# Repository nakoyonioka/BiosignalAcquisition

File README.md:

# Multi-Channel Biosignal Acquisition System with DRL

This project provides a hardware platform for capturing physiological signals such as EEG or ECG. It features multiple input channels with dedicated analog signal conditioning stages (amplification, filtering) to prepare the signals for digitization. A key aspect is the inclusion of a Driven Right Leg (DRL) circuit on Channel 1, a common technique in biopotential measurements to improve signal quality by reducing common-mode interference. The system also incorporates robust power management, supporting battery operation and providing necessary regulated voltage rails, before signals are passed to an Analog-to-Digital Converter (ADC) for digital processing via either isolated or non-isolated SPI.

## Features

- **Multi-Channel Input:** Supports acquisition from 4 independent biosignal channels.
- **Analog Front-End:** Each channel includes amplification and filtering stages (high-pass and low-pass filters).
- **Driven Right Leg (DRL):** Channel 1 features a DRL circuit for enhanced common-mode noise rejection.
- **Signal Conditioning:** Band-pass filtering.
- **Analog-to-Digital Conversion:** Utilizes an onboard ADC (**AD7682BCP**) to convert analog signals to digital data.
- **Digital Interface:** Provides SPI communication interface for connecting to a microcontroller or processor. Includes options for isolated or non-isolated SPI.
- **Power Management:**
  - Battery input and switching.
  - Battery protection IC (BQ29723).
  - Boost converter (TPS61232) for generating +5V from a lower battery voltage.
  - RED3025 and LM2776 IC for generating reference voltagse for ADC and opamps
  - Virtual ground generation for the analog circuitry.

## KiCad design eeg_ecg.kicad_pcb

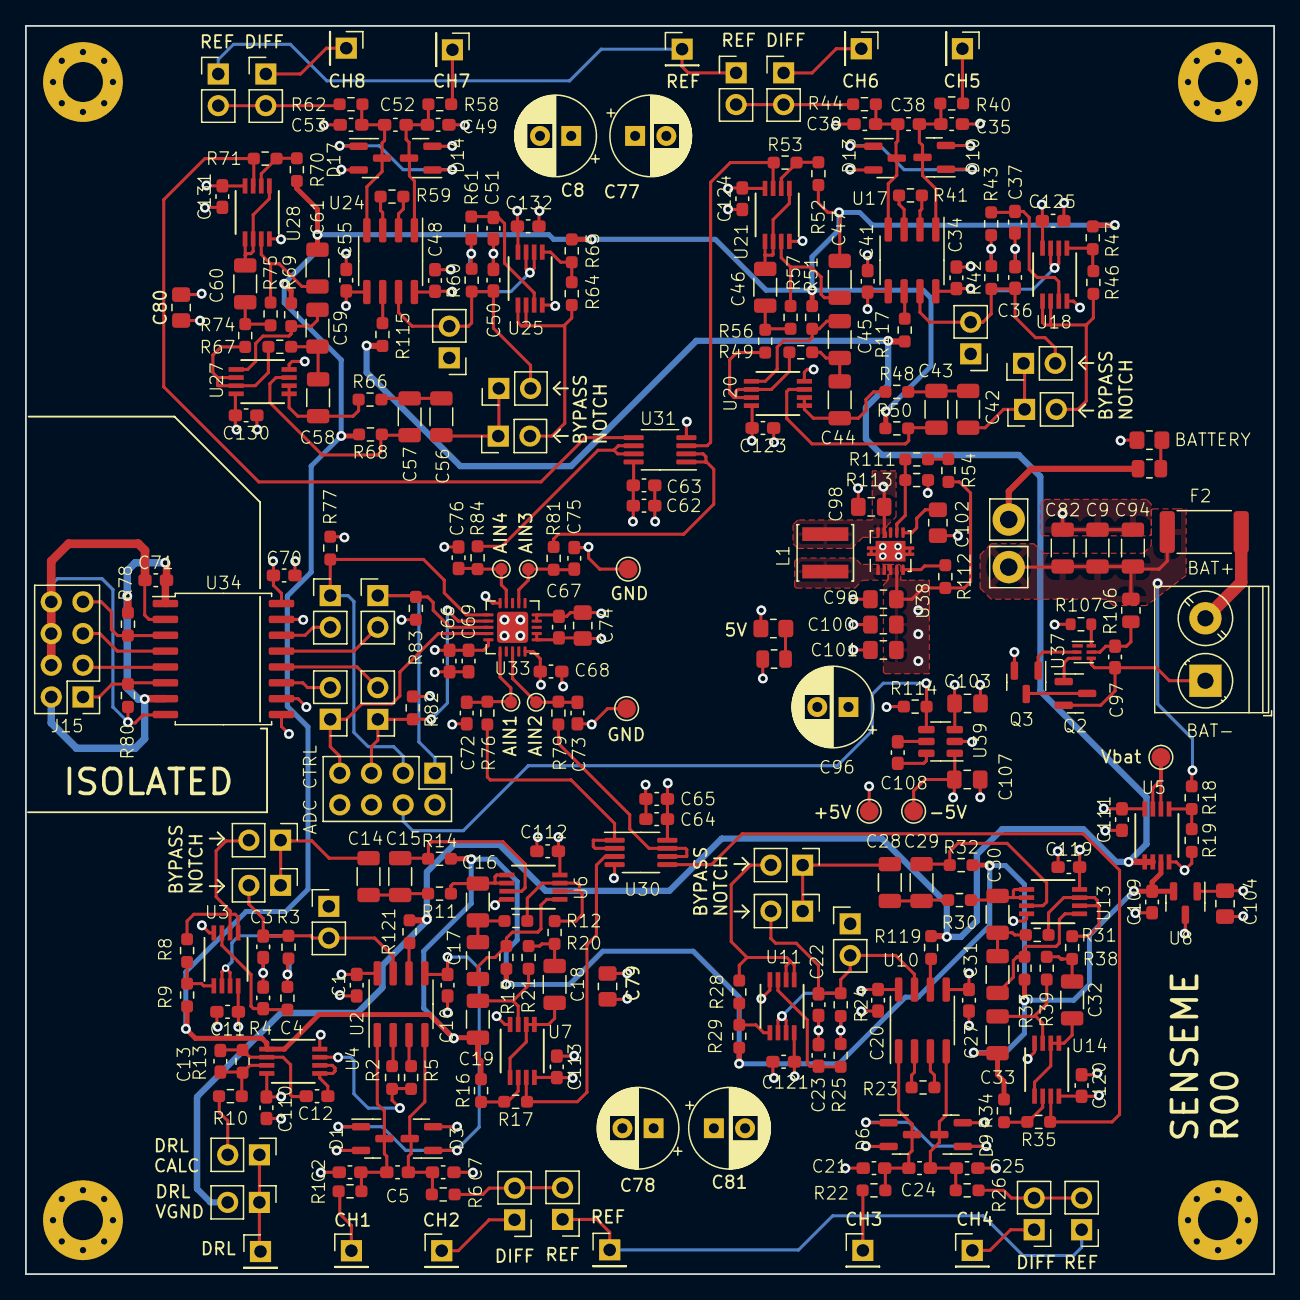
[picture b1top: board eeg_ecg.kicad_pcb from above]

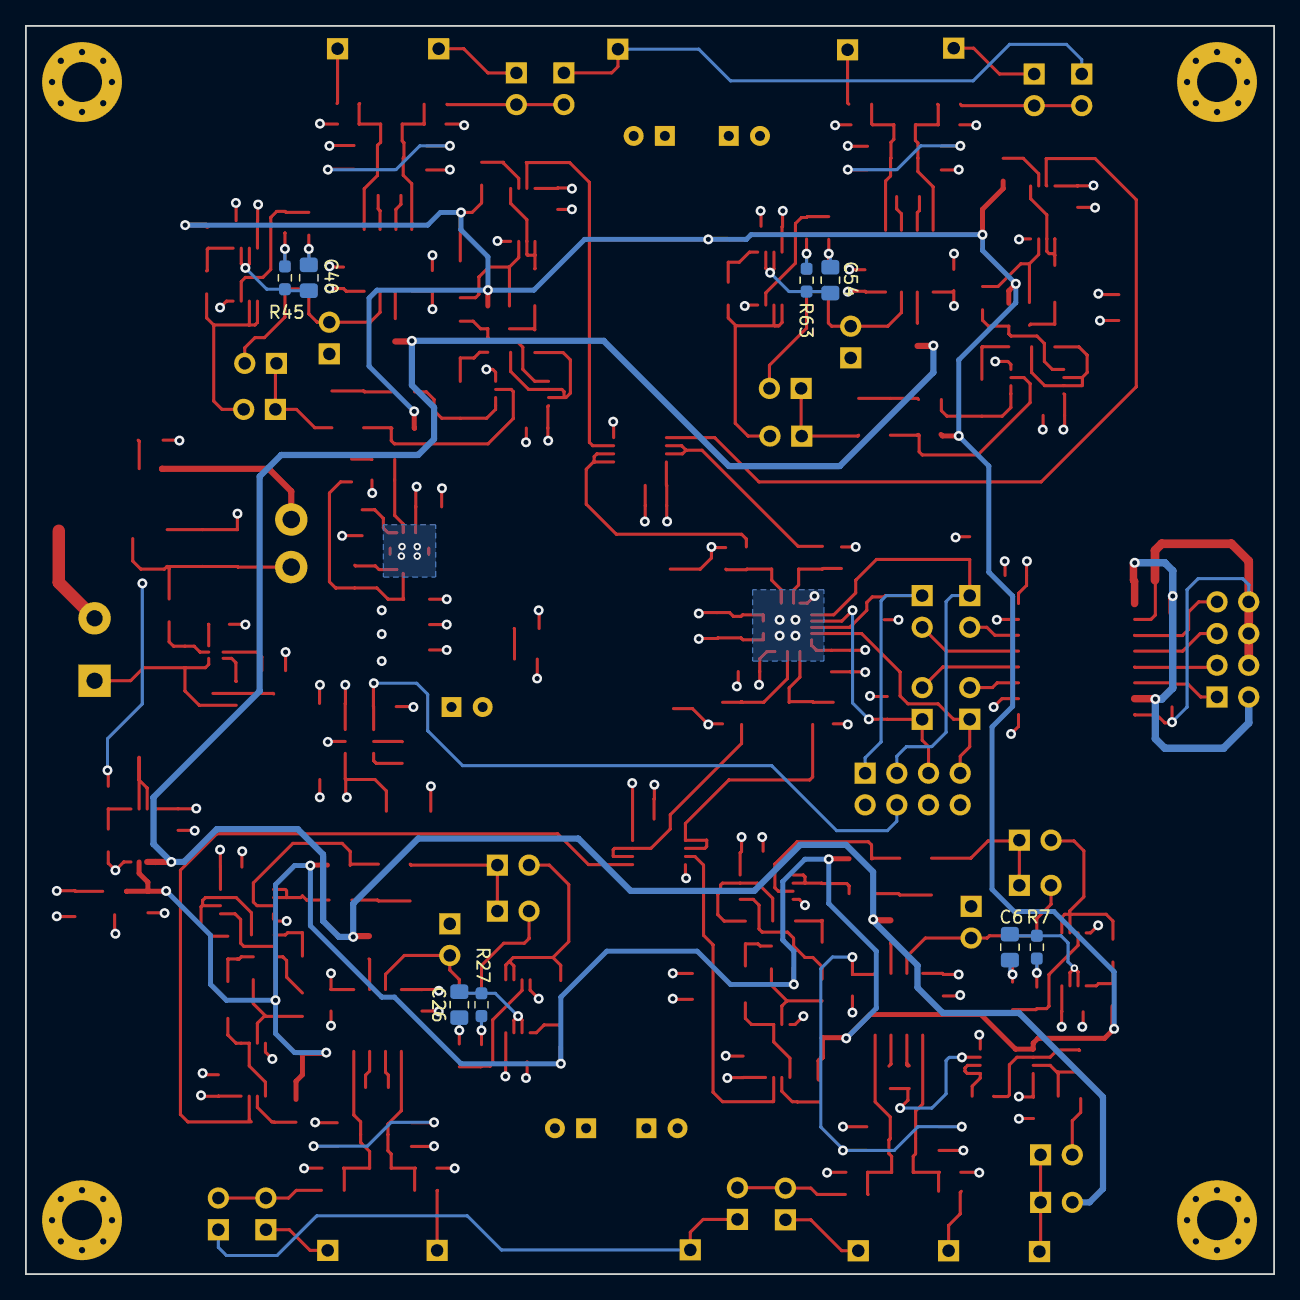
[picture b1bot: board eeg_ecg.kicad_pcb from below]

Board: 4 copper layers, 100.0 x 100.0 mm, 294 parts (8 on the bottom side), 163 nets.

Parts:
C1, C10, C11, C20, C27, C34, C41, C48, C55, C62, C64, C67, C68, C69, C70, C71, C97, C109, C110, C111, C112, C113, C119, C120, C121, C123, C124, C125, C130, C131, C132: 100nF; C_0603_1608Metric_Pad1.08x0.95mm_HandSolder
C2, C7, C21, C25, C35, C39, C49, C53: 100pF; C_0603_1608Metric_Pad1.08x0.95mm_HandSolder
C3, C4, C5, C22, C23, C24, C36, C37, C38, C50, C51, C52: 1nF; C_0603_1608Metric_Pad1.08x0.95mm_HandSolder
C6, C26, C40, C54: 22nF; C_0805_2012Metric_Pad1.18x1.45mm_HandSolder
C8, C77, C78, C81, C96: 100uF; CP_Radial_D6.3mm_P2.50mm
C9, C82, C94: 22uF; C_1206_3216Metric
C12, C108: 1uF; C_0603_1608Metric_Pad1.08x0.95mm_HandSolder
C13: 220nF; C_0603_1608Metric_Pad1.08x0.95mm_HandSolder
C14, C15, C16, C17, C19, C28, C29, C30, C31, C33, C42, C43, C44, C45, C47, C56, C57, C58, C59, C61: 100nF; C_1206_3216Metric
C18, C32, C46, C60: 220nF; C_1206_3216Metric
C63, C65, C66: 10uF; C_0603_1608Metric_Pad1.08x0.95mm_HandSolder
C72, C73, C75, C76: 10nF; C_0603_1608Metric_Pad1.08x0.95mm_HandSolder
C74: 10uF; C_0805_2012Metric_Pad1.18x1.45mm_HandSolder
C79, C80, C98, C99, C100, C101, C103, C104, C107: 22uF; C_0805_2012Metric_Pad1.18x1.45mm_HandSolder
C102: 10nF; C_0805_2012Metric_Pad1.18x1.45mm_HandSolder
D1, D3, D6, D9, D10, D13, D14, D17: BAV199; SOT-23
D2, D4: GREEN; R_0805_2012Metric_Pad1.20x1.40mm_HandSolder
F2: 5A; R_2512_6332Metric
H1, H2, H3, H4: MountingHole_Pad; MountingHole_3.2mm_M3_Pad_Via
J1, J2, J3, J4, J5, J6, J7, J8, J9, J10, J12: Conn_01x01; PinHeader_1x01_P2.54mm_Vertical
J11, J15: Conn_02x04_Odd_Even; PinHeader_2x04_P2.54mm_Vertical
J29, J30: Conn_01x01_Pin; Pin_D1.4mm_L8.5mm_W2.8mm_FlatFork
J33: Screw_Terminal_01x02; TerminalBlock_Phoenix_PT-1,5-2-5.0-H_1x02_P5.00mm_Horizontal
JP1, JP2, JP3, JP4, JP5, JP6, JP7, JP8, JP9, JP10, JP11, JP12, JP13, JP14, JP15, JP16, JP17, JP18, JP19, JP20, JP21, JP22, JP31, JP32, JP33, JP34: Jumper_2_Open; PinHeader_1x02_P2.54mm_Vertical
L1: SWPA4030S1R0NT/1uH; L_Sunlord_SWPA4030S
Q2, Q3: AO3400A; SOT-23
R1, R6, R18, R19, R22, R26, R40, R44, R58, R62, R77, R78, R80, R82, R83, R114: 10k; R_0603_1608Metric_Pad0.98x0.95mm_HandSolder
R2, R5: 220; R_0603_1608Metric_Pad0.98x0.95mm_HandSolder
R3, R4, R24, R25, R42, R43, R60, R61, R111: 330k; R_0603_1608Metric_Pad0.98x0.95mm_HandSolder
R7, R27, R45, R63: 150k; R_0603_1608Metric_Pad0.98x0.95mm_HandSolder
R8, R28, R46, R64: 20k; R_0603_1608Metric_Pad0.98x0.95mm_HandSolder
R9, R15, R29, R33, R47, R51, R65, R69: 82k; R_0603_1608Metric_Pad0.98x0.95mm_HandSolder
R10, R17, R35, R53, R71, R113: 100k; R_0603_1608Metric_Pad0.98x0.95mm_HandSolder
R11, R30, R48, R66: 30k; R_0603_1608Metric_Pad0.98x0.95mm_HandSolder
R12, R31, R49, R67: 12k; R_0603_1608Metric_Pad0.98x0.95mm_HandSolder
R13, R112: 1Meg; R_0603_1608Metric_Pad0.98x0.95mm_HandSolder
R14, R32, R50, R68: 33k; R_0603_1608Metric_Pad0.98x0.95mm_HandSolder
R16, R34, R52, R70: 1k; R_0603_1608Metric_Pad0.98x0.95mm_HandSolder
R20, R21, R38, R39, R56, R57, R74, R75: 15k; R_0603_1608Metric_Pad0.98x0.95mm_HandSolder
R23, R41, R59: 510; R_0603_1608Metric_Pad0.98x0.95mm_HandSolder
R36, R37, R106: 330R; R_0805_2012Metric
R54: 75k; R_0603_1608Metric_Pad0.98x0.95mm_HandSolder
R76, R79, R81, R84: 100; R_0603_1608Metric_Pad0.98x0.95mm_HandSolder
R107: 2k7; R_0603_1608Metric
R115, R117, R119, R121: 0R; R_0603_1608Metric_Pad0.98x0.95mm_HandSolder
TP1, TP2, TP3, TP4, TP5: TestPoint; TestPoint_Pad_D1.5mm
TP6, TP7, TP8, TP9: TestPoint; TestPoint_Pad_D1.0mm
U2, U10, U17, U24: AD8421ARZ; SOIC-8_3.9x4.9mm_P1.27mm
U3, U4, U5, U6, U7, U11, U13, U14, U18, U20, U21, U25, U27, U28: AD8606ARMZ-R7; AD8606ARMZ
U8: REF3025; SOT-23
U30, U31: ADA4807-2ARM; MSOP-8_3x3mm_P0.65mm
U33: AD7682BCP; LFCSP-20-1EP_4x4mm_P0.5mm_EP2.5x2.5mm
U34: ISO7341C; SOIC-16W_7.5x10.3mm_P1.27mm
U37: BQ29723; WSON-6_1.5x1.5mm_P0.5mm
U38: TPS61230DRC; Texas_S-PVSON-N10_ThermalVias
U39: LM2776; SOT-23-6

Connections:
+5V: C1.2, C8.1, C11.2, C20.2, C34.2, C48.2, C62.2, C63.2, C64.2, C65.2, C66.2, C67.2, C68.2, C69.2, C70.2, C74.2, C77.1, C78.1, C81.1, C96.1, C99.2, C100.2, C101.2, C103.2, C104.2, C110.2, C111.2, C112.2, C113.2, C119.2, C120.2, C121.2, C123.2, C124.2, C125.2, C130.2, C131.2, C132.2, D1.2 (K), D3.2 (K), D6.2 (K), D9.2 (K), D10.2 (K), D13.2 (K), D14.2 (K), D17.2 (K), J11.2, R36.1, R54.1, R77.1, R112.2, R114.1, TP2.1, U2.8 (Vs+), U3.8 (V+), U4.8 (V+), U5.8 (V+), U6.8 (V+), U7.8 (V+), U8.1 (IN), U10.8 (Vs+), U11.8 (V+), U13.8 (V+), U14.8 (V+), U17.8 (Vs+), U18.8 (V+), U20.8 (V+), U21.8 (V+), U24.8 (Vs+), U25.8 (V+), U27.8 (V+), U28.8 (V+), U30.8 (V+), U31.8 (V+), U33.1 (VDD), U33.2 (REF), U33.15 (VIO), U33.20 (VDD), U34.10 (EN2), U34.16 (VCC2), U38.3 (VOUT), U38.4 (VOUT), U39.3 (VIN)
+5VP: C71.2, J15.2, R78.1, U34.1 (VCC1), U34.7 (EN1)
+BATT: C9.1, C82.1, C94.1, F2.2, J29.1, R18.1, R106.2
-5V: C10.2, C27.2, C41.2, C55.2, C79.2, C80.2, C107.2, D1.1 (A), D3.1 (A), D6.1 (A), D9.1 (A), D10.1 (A), D13.1 (A), D14.1 (A), D17.1 (A), TP3.1, U2.5 (Vs-), U10.5 (Vs-), U17.5 (Vs-), U24.5 (Vs-), U39.1 (VOUT)
/ADC and control/ADCCLK: J11.1, JP20.1 (A), R83.1, U33.13 (SCK)
/ADC and control/ADCCSn: J11.3, JP19.1 (A), R77.2, U33.11 (CNV)
/ADC and control/ADCDIN: J11.5, JP21.1 (A), R82.1, U33.12 (DIN)
/ADC and control/ADCDO: J11.7, JP22.1 (A), U33.14 (SDO)
/ADC and control/AIN1: C72.2, R76.1, TP6.1, U33.16 (IN0)
/ADC and control/AIN2: C73.2, R79.1, TP7.1, U33.18 (IN1)
/ADC and control/AIN3: C75.2, R81.1, TP8.1, U33.7 (IN2)
/ADC and control/AIN4: C76.2, R84.1, TP9.1, U33.9 (IN3)
/ADC and control/CH1: R17.1, U7.7, U30.3 (+)
/ADC and control/CH2: R35.1, U14.7, U30.5 (+)
/ADC and control/CH3: R53.1, U21.7, U31.3 (+)
/ADC and control/CH4: R71.1, U28.7, U31.5 (+)
/ADC and control/ISO_CLK: J15.5, U34.4 (INB)
/ADC and control/ISO_CSn: J15.7, R78.2, U34.3 (INA)
/ADC and control/ISO_MISO: J15.1, R80.1, U34.6 (OUTD)
/ADC and control/ISO_MOSI: J15.3, U34.5 (INC)
/Battery input/BATn: C97.2, J33.1, Q2.2 (S), U37.4 (VSS)
/Battery input/BATp: F2.1, J33.2
/Battery input/Vbat: TP1.1, U5.6 (-), U5.7
/Channel 1 with DRL option/DRL: J6.1, JP5.1 (A), JP6.1 (A)
/Channel 1 with DRL option/HPF1: R12.1, R20.2, U6.6 (-), U6.7
/Channel 1 with DRL option/INPUT1: J1.1, R1.1
/Channel 1 with DRL option/INPUT2: J2.1, JP2.1 (A)
/Channel 1 with DRL option/NOTCH1: JP3.2 (B), R8.1, U3.1, U3.2 (-)
/Channel 2/HPF2: R31.1, R38.2, U13.6 (-), U13.7
/Channel 2/INPUT3: J4.1, R22.1
/Channel 2/INPUT4: J5.1, JP8.1 (A)
/Channel 2/NOTCH2: JP11.2 (B), R28.1, U11.1, U11.2 (-)
/Channel 3/HPF3: R49.1, R56.2, U20.6 (-), U20.7
/Channel 3/INPUT5: J7.1, R40.1
/Channel 3/INPUT6: J8.1, JP12.1 (A)
/Channel 3/NOTCH3: JP17.2 (B), R46.1, U18.1, U18.2 (-)
/Channel 4/HPF4: R67.1, R74.2, U27.6 (-), U27.7
/Channel 4/INPUT7: J9.1, R58.1
/Channel 4/INPUT8: J10.1, JP16.1 (A)
/Channel 4/NOTCH4: JP33.2 (B), R64.1, U25.1, U25.2 (-)
/Power supply/EN5V: J11.4, R114.2, U39.4 (EN)
GND: C1.1, C2.1, C7.2, C8.2, C9.2, C10.1, C11.1, C20.1, C21.1, C25.2, C27.1, C34.1, C35.1, C39.2, C41.1, C48.1, C49.1, C53.2, C55.1, C62.1, C63.1, C64.1, C65.1, C66.1, C67.1, C68.1, C69.1, C70.1, C72.1, C73.1, C74.1, C75.1, C76.1, C77.2, C78.2, C79.1, C80.1, C81.2, C82.2, C94.2, C96.2, C98.1, C99.1, C100.1, C101.1, C102.1, C103.1, C104.1, C107.1, C109.1, C110.1, C111.1, C112.1, C113.1, C119.1, C120.1, C121.1, C123.1, C124.1, C125.1, C130.1, C131.1, C132.1, D2.1 (K), D4.1 (K), H1.1, H2.1, H3.1, H4.1, J11.6, J11.8, JP1.1 (A), JP9.1 (A), JP15.1 (A), JP32.1 (A), Q3.2 (S), R19.2, R82.2, R83.2, R107.1, R113.2, TP4.1, TP5.1, U3.4 (V-), U4.4 (V-), U5.4 (V-), U6.4 (V-), U7.4 (V-), U8.3 (GND), U11.4 (V-), U13.4 (V-), U14.4 (V-), U18.4 (V-), U20.4 (V-), U21.4 (V-), U25.4 (V-), U27.4 (V-), U28.4 (V-), U30.4 (V-), U31.4 (V-), U33.4 (GND), U33.5 (GND), U33.10 (COM), U33.21 (EPAD), U34.9 (GND2), U34.15 (GND2), U38.11 (GND), U39.2 (GND)
GNDPWR: C71.1, J15.4, J15.6, J15.8, R80.2, U34.2 (GND1), U34.8 (GND1)
unnamed: C3.2, C4.1, R7.1
unnamed: C6.2, R3.1, R4.2
unnamed: C13.2, R10.2, R13.1, U4.7
unnamed: C14.1, C15.2, R11.2
unnamed: C16.1, C17.2, R12.2
unnamed: C18.1, R20.1, R21.2
unnamed: C22.2, C23.1, R27.1
unnamed: C26.2, R24.1, R25.2
unnamed: C28.1, C29.2, R30.2
unnamed: C30.1, C31.2, R31.2
unnamed: C32.1, R38.1, R39.2
unnamed: C36.2, C37.1, R45.1
unnamed: C40.2, R42.1, R43.2
unnamed: C42.1, C43.2, R48.2
unnamed: C44.1, C45.2, R49.2
unnamed: C46.1, R56.1, R57.2
unnamed: C50.2, C51.1, R63.1
unnamed: C54.2, R60.1, R61.2
unnamed: C56.1, C57.2, R66.2
unnamed: C58.1, C59.2, R67.2
unnamed: C60.1, R74.1, R75.2
unnamed: C2.2, C5.1, D1.3 (common), R1.2, U2.1 (-)
unnamed: D2.2 (A), R36.2
unnamed: C5.2, C7.1, D3.3 (common), R6.2, U2.4 (+)
unnamed: D4.2 (A), R37.2
unnamed: C21.2, C24.1, D6.3 (common), R22.2, U10.1 (-)
unnamed: C24.2, C25.1, D9.3 (common), R26.2, U10.4 (+)
unnamed: C35.2, C38.1, D10.3 (common), R40.2, U17.1 (-)
unnamed: C38.2, C39.1, D13.3 (common), R44.2, U17.4 (+)
unnamed: C49.2, C52.1, D14.3 (common), R58.2, U24.1 (-)
unnamed: C52.2, C53.1, D17.3 (common), R62.2, U24.4 (+)
unnamed: C3.1, JP1.2 (B), JP7.2 (B), R3.2, U2.7
unnamed: JP2.2 (B), JP4.2 (B), R6.1
unnamed: C14.2, JP3.1 (A), JP7.1 (A)
unnamed: JP5.2 (B), R10.1
unnamed: JP8.2 (B), JP10.2 (B), R26.1
unnamed: C28.2, JP11.1 (A), JP13.1 (A)
unnamed: JP12.2 (B), JP14.2 (B), R44.1
unnamed: C22.1, JP9.2 (B), JP13.2 (B), R24.2, U10.7
unnamed: C36.1, JP15.2 (B), JP31.2 (B), R42.2, U17.7
unnamed: JP16.2 (B), JP18.2 (B), R62.1
unnamed: C42.2, JP17.1 (A), JP31.1 (A)
unnamed: JP19.2 (B), U34.14 (OUTA)
unnamed: JP20.2 (B), U34.13 (OUTB)
unnamed: JP21.2 (B), U34.12 (OUTC)
unnamed: JP22.2 (B), U34.11 (IND)
unnamed: C50.1, JP32.2 (B), JP34.2 (B), R60.2, U24.7
unnamed: C56.2, JP33.1 (A), JP34.1 (A)
unnamed: L1.2, U38.1 (SW), U38.2 (SW)
unnamed: Q2.3 (D), Q3.3 (D)
unnamed: Q2.1 (G), U37.3 (Dout)
unnamed: Q3.1 (G), U37.2 (Cout)
unnamed: R2.2, U2.2 (Rg)
unnamed: R5.2, U2.3 (Rg)
unnamed: R23.1, U10.3 (Rg)
unnamed: R23.2, U10.2 (Rg)
unnamed: R41.1, U17.3 (Rg)
unnamed: R41.2, U17.2 (Rg)
unnamed: R59.1, U24.3 (Rg)
unnamed: R59.2, U24.2 (Rg)
unnamed: R54.2, R111.1
unnamed: R121.2, U2.6 (Ref)
unnamed: C4.2, R4.1, U3.3 (+)
unnamed: R8.2, R9.1, U3.5 (+)
unnamed: C6.1, R7.2, U3.6 (-), U3.7
unnamed: R2.1, R5.1, U4.3 (+)
unnamed: C12.2, U4.1, U4.2 (-)
unnamed: C12.1, C13.1, R13.2, U4.6 (-)
unnamed: R18.2, R19.1, U5.5 (+)
unnamed: C15.1, R14.1, U6.3 (+)
unnamed: C16.2, R11.1, U6.1, U6.2 (-)
unnamed: C17.1, R15.1, U6.5 (+)
unnamed: C19.2, R21.1, U7.3 (+)
unnamed: C18.2, U7.1, U7.2 (-), U7.5 (+)
unnamed: R16.1, R17.2, U7.6 (-)
unnamed: R119.2, U10.6 (Ref)
unnamed: C23.2, R25.1, U11.3 (+)
unnamed: R28.2, R29.1, U11.5 (+)
unnamed: C26.1, R27.2, U11.6 (-), U11.7
unnamed: C29.1, R32.1, U13.3 (+)
unnamed: C30.2, R30.1, U13.1, U13.2 (-)
unnamed: C31.1, R33.1, U13.5 (+)
unnamed: C33.2, R39.1, U14.3 (+)
unnamed: C32.2, U14.1, U14.2 (-), U14.5 (+)
unnamed: R34.1, R35.2, U14.6 (-)
unnamed: R117.2, U17.6 (Ref)
unnamed: C37.2, R43.1, U18.3 (+)
unnamed: R46.2, R47.1, U18.5 (+)
unnamed: C40.1, R45.2, U18.6 (-), U18.7
unnamed: C43.1, R50.1, U20.3 (+)
unnamed: C44.2, R48.1, U20.1, U20.2 (-)
unnamed: C45.1, R51.1, U20.5 (+)
unnamed: C47.2, R57.1, U21.3 (+)
unnamed: C46.2, U21.1, U21.2 (-), U21.5 (+)
unnamed: R52.1, R53.2, U21.6 (-)
unnamed: R115.2, U24.6 (Ref)
unnamed: C51.2, R61.1, U25.3 (+)
unnamed: R64.2, R65.1, U25.5 (+)
unnamed: C54.1, R63.2, U25.6 (-), U25.7
unnamed: C57.1, R68.1, U27.3 (+)
unnamed: C58.2, R66.1, U27.1, U27.2 (-)
unnamed: C59.1, R69.1, U27.5 (+)
unnamed: C61.2, R75.1, U28.3 (+)
unnamed: C60.2, U28.1, U28.2 (-), U28.5 (+)
unnamed: R70.1, R71.2, U28.6 (-)
unnamed: R76.2, U30.1, U30.2 (-)
unnamed: R79.2, U30.6 (-), U30.7
unnamed: R81.2, U31.1, U31.2 (-)
unnamed: R84.2, U31.6 (-), U31.7
unnamed: C97.1, R106.1, U37.5 (BAT)
unnamed: R107.2, U37.6 (V-)
unnamed: R111.2, R113.1, U38.7 (FB)
unnamed: R112.1, U38.5 (PG)
unnamed: C102.2, U38.6 (SS)
unnamed: C108.2, U39.5 (C1+)
unnamed: C108.1, U39.6 (C1-)
REFCH: J3.1, J12.1, JP4.1 (A), JP10.1 (A), JP14.1 (A), JP18.1 (A)
VCC: C98.2, J30.1, L1.1, R37.1, U38.9 (EN), U38.10 (VIN)
VPP: JP6.2 (B), R115.1, R117.1, R119.1, R121.1, U5.1, U5.2 (-)
Vdrive: C19.1, C33.1, C47.1, C61.1, C109.2, R9.2, R14.2, R15.2, R16.2, R29.2, R32.2, R33.2, R34.2, R47.2, R50.2, R51.2, R52.2, R65.2, R68.2, R69.2, R70.2, U4.5 (+), U5.3 (+), U8.2 (OUT)

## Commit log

2025-05-06 publish design files
2025-05-06 publish pdf
